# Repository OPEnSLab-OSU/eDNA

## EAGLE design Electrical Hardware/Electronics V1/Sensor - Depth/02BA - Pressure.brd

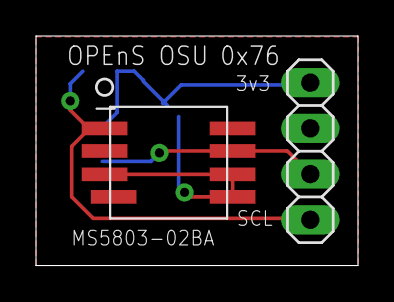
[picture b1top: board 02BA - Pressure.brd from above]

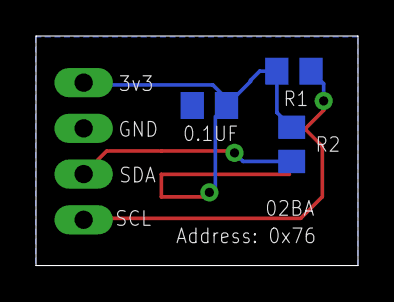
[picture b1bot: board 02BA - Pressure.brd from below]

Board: 2 copper layers, 17.9 x 12.8 mm, 5 parts (3 on the bottom side), 4 nets.

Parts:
0.1UF: 100nF; C0805
JP1: 1X04
PRESSURE: MS5803-01BA; SMD
R1, R2: 7.7k; R0805

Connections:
+3V3: 0.1UF.2, JP1.1, PRESSURE.CSB, PRESSURE.PS, PRESSURE.VDD, R1.2, R2.2
GND: 0.1UF.1, JP1.2
SCL: JP1.4, PRESSURE.SCLK, R1.1
SDA: JP1.3, PRESSURE.SDI/SDA, R2.1

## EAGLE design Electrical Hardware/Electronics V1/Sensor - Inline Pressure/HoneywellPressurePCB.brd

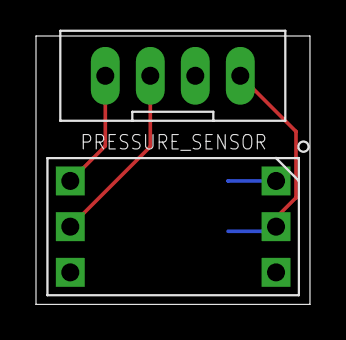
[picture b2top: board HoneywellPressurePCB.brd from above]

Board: 2 copper layers, 15.2 x 14.9 mm, 3 parts (1 on the bottom side), 4 nets.

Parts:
0.1UF: C1206
JST: JST_4POS_2.5MM_UP
PRESSURE_SENSOR: HONEYWELL_PRESSURE_SENSOR; DIP6

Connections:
3V3: 0.1UF.2, JST.4, PRESSURE_SENSOR.2
GND: 0.1UF.1, JST.3, PRESSURE_SENSOR.1
SCL: JST.1, PRESSURE_SENSOR.6
SDA: JST.2, PRESSURE_SENSOR.5

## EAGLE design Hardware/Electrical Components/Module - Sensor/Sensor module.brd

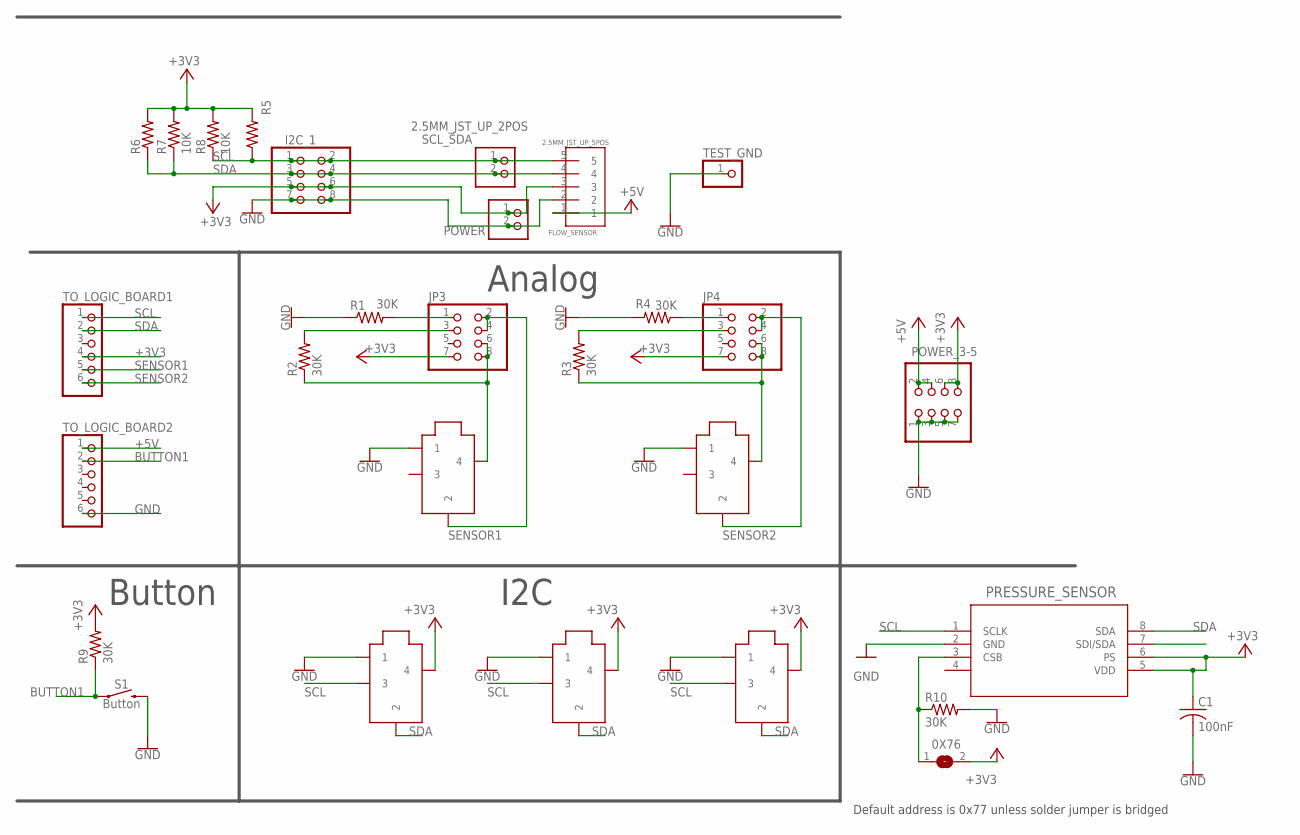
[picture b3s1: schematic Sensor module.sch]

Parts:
0X76: SJ
ANALOG1, ANALOG2: AUDIOJACK_2.5MM_SMD; AJ_2.5_SMD
C1: 100nF; C1206
FLOW_SENSOR: 2.5MM_JST_UP_5POS; JST_5POS_2.5MM_UP
I2C_1: PINHD-2X4; 2X04
JP3, JP4: PINHD-2X4; 2X04
POWER: 2.5MM_JST_UP_2POS; JST_2POS_2.5MM_UP
POWER_3-5: PINHD-2X4; 2X04
PRESSURE_SENSOR: MS580302BA01-00; MS5803-02BA01
R1, R2, R3, R4, R9, R10: 30K; R1206
R5, R6: R-US_R1206; R1206
R7, R8: 10K; 0204/7
S1: Button; TACTILE_SWITCH_PTH_6.0MM
SCL_SDA: 2.5MM_JST_UP_2POS; JST_2POS_2.5MM_UP
TEST_GND: PINHD-1X1; 1X01
TO_LOGIC_BOARD1, TO_LOGIC_BOARD2: PINHD-1X6CB; 1X06-CLEANBIG
U$1, U$2, U$5: I2C; AJ_2.5_SMD

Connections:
+3V3: 0X76.2, C1.1, FLOW_SENSOR.3, I2C_1.5, I2C_1.6, JP3.7, JP4.7, POWER.1, POWER_3-5.6, POWER_3-5.8, PRESSURE_SENSOR.5 (VDD), PRESSURE_SENSOR.6 (PS), R5.2, R6.2, R7.2, R8.2, R9.2, TO_LOGIC_BOARD1.4, U$1.4, U$2.4, U$5.4
+5V: FLOW_SENSOR.1, POWER_3-5.2, POWER_3-5.4, TO_LOGIC_BOARD2.1
BUTTON1: R9.1, S1.1, TO_LOGIC_BOARD2.2
GND: ANALOG1.1, ANALOG2.1, C1.2, FLOW_SENSOR.2, I2C_1.7, I2C_1.8, POWER.2, POWER_3-5.1, POWER_3-5.3, POWER_3-5.5, POWER_3-5.7, PRESSURE_SENSOR.2 (GND), R1.1, R4.2, R10.2, S1.3 (2), TEST_GND.1, TO_LOGIC_BOARD2.6, U$1.1, U$2.1, U$5.1
unnamed: 0X76.1, PRESSURE_SENSOR.3 (CSB), R10.1
unnamed: ANALOG1.4, JP3.6, JP3.8, R2.1
unnamed: JP3.3, R2.2
unnamed: JP3.1, R1.2
unnamed: JP4.3, R3.2
unnamed: ANALOG2.4, JP4.6, JP4.8, R3.1
unnamed: JP4.1, R4.1
SCL: FLOW_SENSOR.5, I2C_1.1, I2C_1.2, PRESSURE_SENSOR.1 (SCLK), R5.1, R8.1, SCL_SDA.1, TO_LOGIC_BOARD1.1, U$1.3, U$2.3, U$5.3
SDA: FLOW_SENSOR.4, I2C_1.3, I2C_1.4, PRESSURE_SENSOR.8 (SDA), R6.1, R7.1, SCL_SDA.2, TO_LOGIC_BOARD1.2, U$1.2, U$2.2, U$5.2
SENSOR1: ANALOG1.2, JP3.2, JP3.4, TO_LOGIC_BOARD1.5
SENSOR2: ANALOG2.2, JP4.2, JP4.4, TO_LOGIC_BOARD1.6

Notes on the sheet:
I2C
Analog
Button
Default address is 0x77 unless solder jumper is bridged

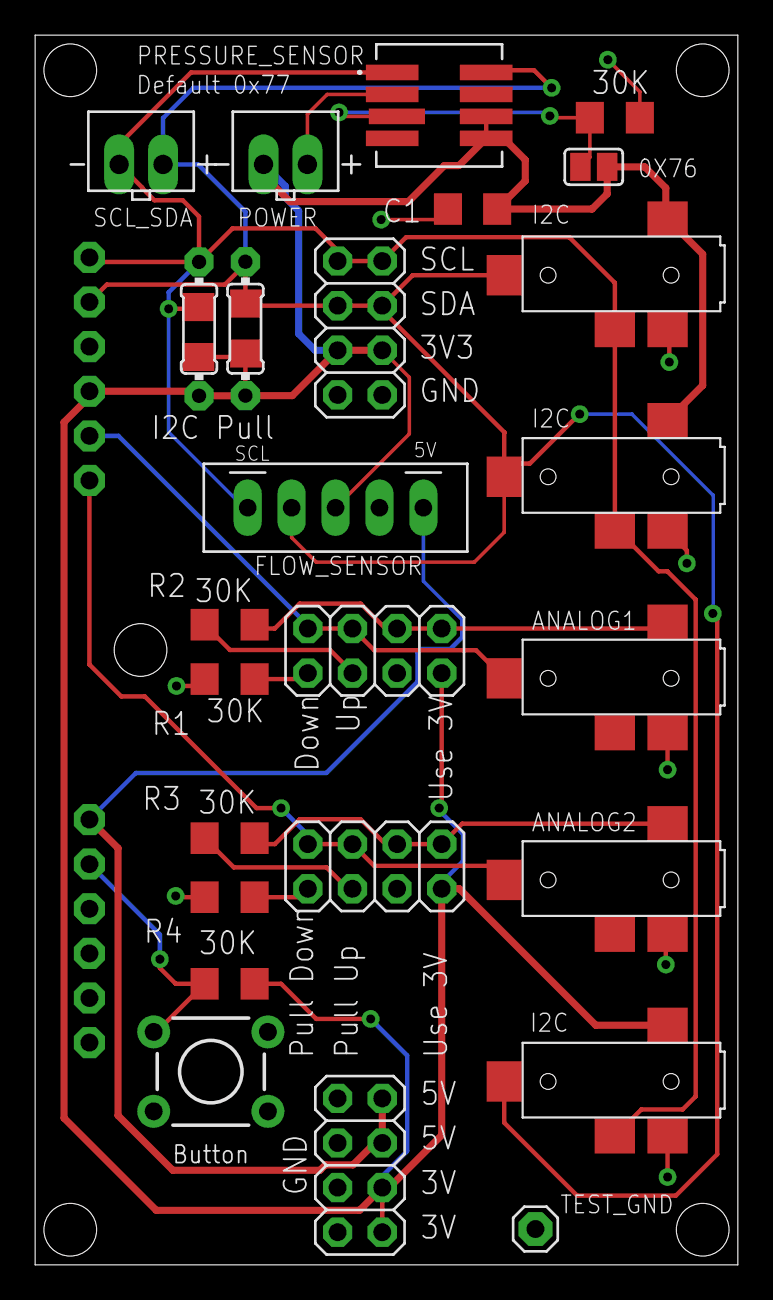
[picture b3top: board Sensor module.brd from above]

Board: 2 copper layers, 40.0 x 70.0 mm, 29 parts (0 on the bottom side), 15 nets.

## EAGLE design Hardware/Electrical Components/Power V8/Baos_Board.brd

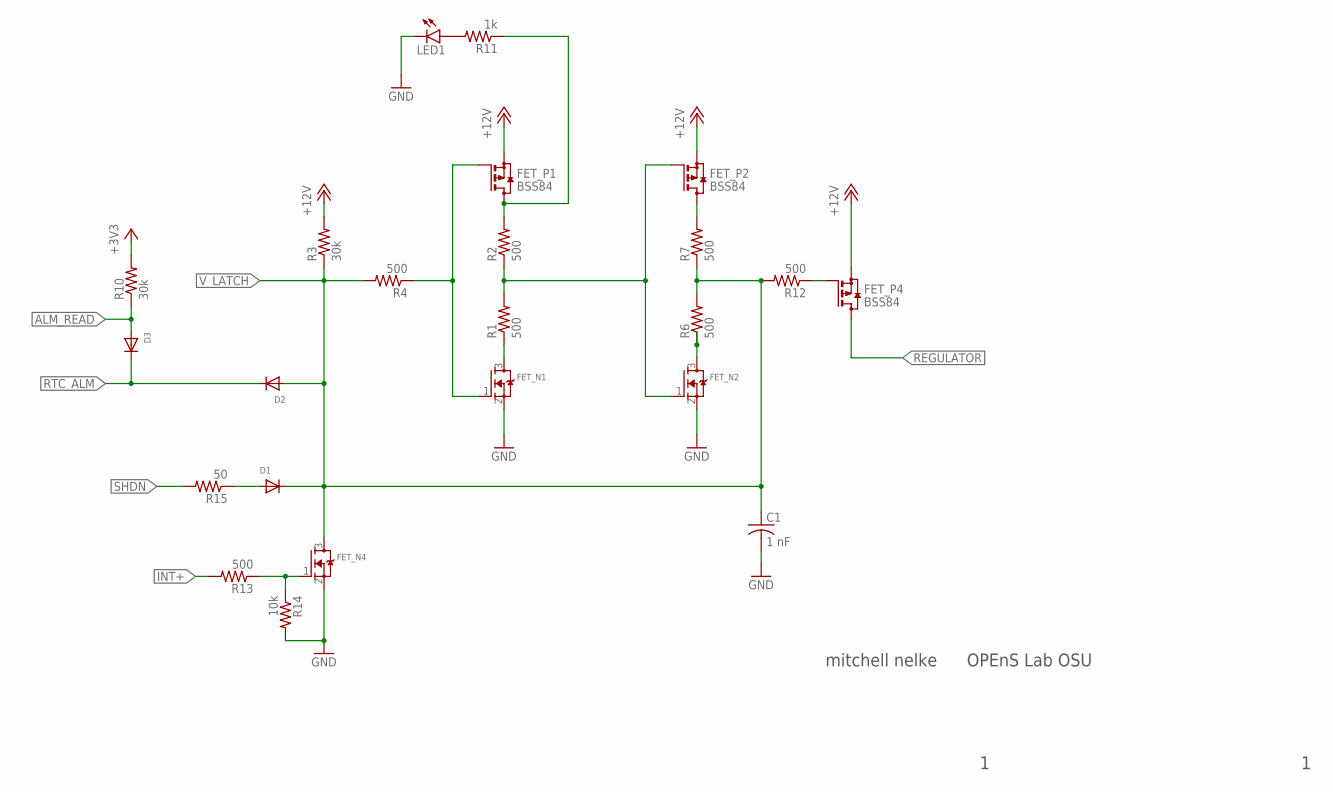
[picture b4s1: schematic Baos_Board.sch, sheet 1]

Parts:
C1: 1 nF; C0805
D1, D2, D3: DIODESOD-123; SOD-123
FET_N1, FET_N2, FET_N4: MOSFET-NREFLOW; SOT23
FET_P1, FET_P2, FET_P4: BSS84; SOT23
LED1: LEDSMT1206; 1206
R1, R2, R4, R6, R7, R12, R13: 500; R0805
R3, R10: 30k; R0805
R11: 1k; R0805
R14: 10k; R0805
R15: 50; R0805

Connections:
+3V3: R10.2; also elsewhere on the board
+12V: FET_P1.2 (S), FET_P2.2 (S), FET_P4.2 (S), R3.2; also elsewhere on the board
ALM_READ: D3.A, R10.1; also elsewhere on the board
GND: C1.2, FET_N1.2 (S), FET_N2.2 (S), FET_N4.2 (S), LED1.C, R14.2; also elsewhere on the board
INT+: R13.2
unnamed: FET_P1.3 (D), R2.2, R11.1
unnamed: FET_N1.3 (D), R1.1
unnamed: FET_N1.1 (G), FET_P1.1 (G), R4.1
unnamed: FET_N2.1 (G), FET_P2.1 (G), R1.2, R2.1
unnamed: FET_P2.3 (D), R7.2
unnamed: FET_N2.3 (D), R6.1
unnamed: LED1.A, R11.2
unnamed: FET_P4.1 (G), R12.1
unnamed: D1.A, R15.1
unnamed: FET_N4.1 (G), R13.1, R14.1
REGULATOR: FET_P4.3 (D); also elsewhere on the board
RTC_ALM: D2.C, D3.C; also elsewhere on the board
SHDN: R15.2; also elsewhere on the board
V_LATCH: C1.1, D1.C, D2.A, FET_N4.3 (D), R3.1, R4.2, R6.2, R7.1, R12.2; also elsewhere on the board

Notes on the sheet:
mitchell nelke
OPEnS Lab OSU

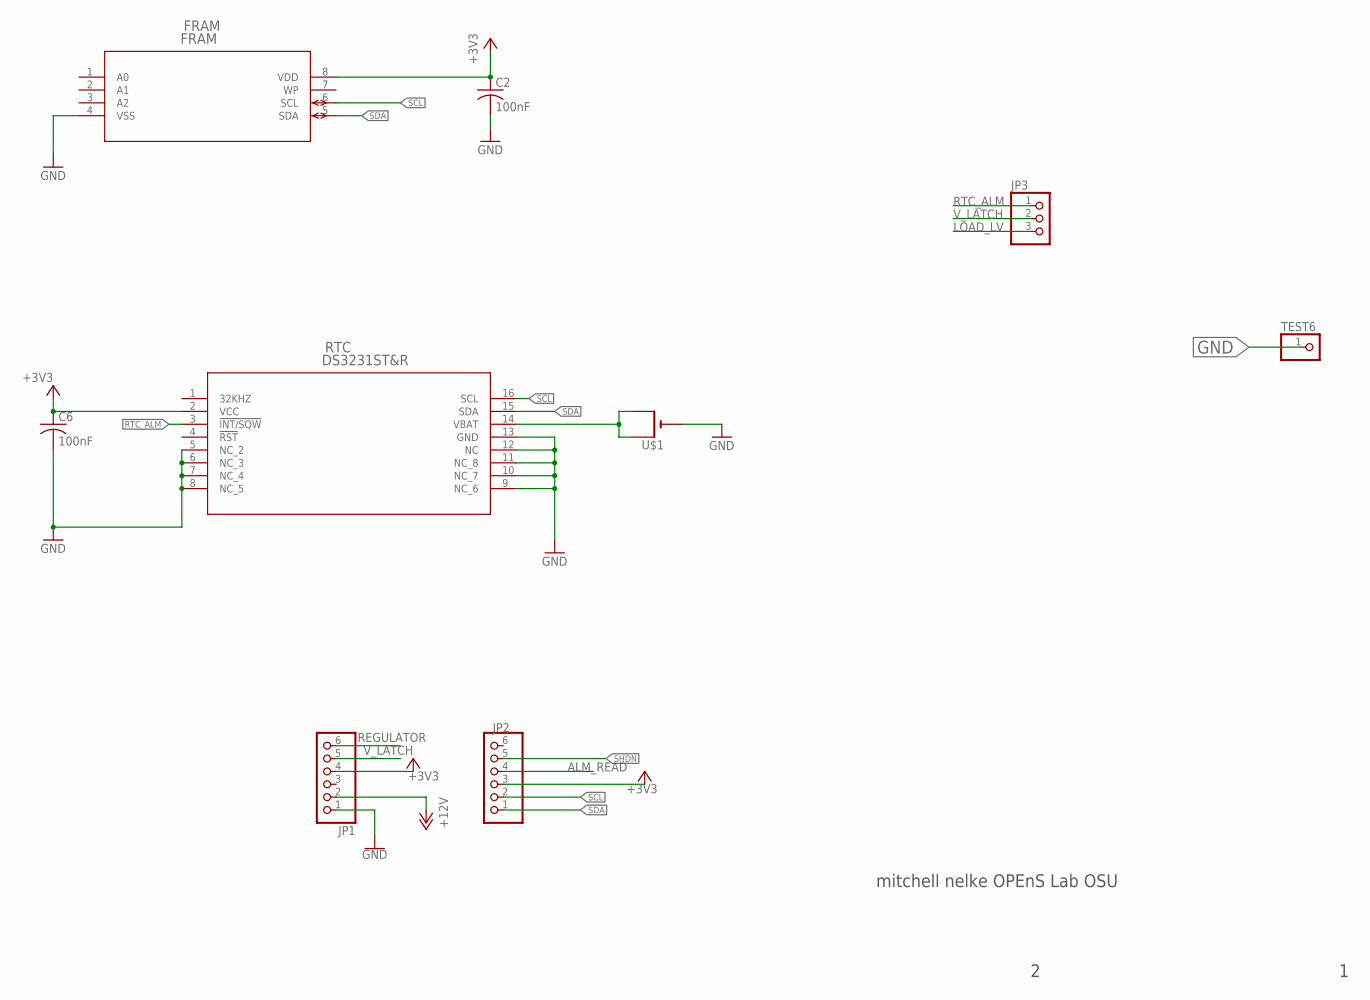
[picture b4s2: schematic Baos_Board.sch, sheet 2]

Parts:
C2, C6: 100nF; C0805
FRAM: FRAM; FPT-8P-M02
JP1, JP2: PINHD-1X6; 1X06
JP3: PINHD-1X3; 1X03
RTC: DS3231ST&R; 21-0042B_16
TEST6: PINHD-1X1; 1X01
U$1: CR1220SMT; CR1220-SMD

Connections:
+3V3: C2.1, C6.1, FRAM.8 (VDD), JP1.4, JP2.3, RTC.2 (VCC); also elsewhere on the board
+12V: JP1.2; also elsewhere on the board
ALM_READ: JP2.4; also elsewhere on the board
GND: C2.2, C6.2, FRAM.4 (VSS), JP1.1, RTC.5 (NC_2), RTC.6 (NC_3), RTC.7 (NC_4), RTC.8 (NC_5), RTC.9 (NC_6), RTC.10 (NC_7), RTC.11 (NC_8), RTC.12 (NC), RTC.13 (GND), TEST6.1, U$1.-; also elsewhere on the board
LOAD_LV: JP3.3
unnamed: RTC.14 (VBAT), U$1.+$1 (+), U$1.+$2 (+1)
REGULATOR: JP1.6; also elsewhere on the board
RTC_ALM: JP3.1, RTC.3 (!INT/SQW); also elsewhere on the board
SCL: FRAM.6 (SCL), JP2.2, RTC.16 (SCL)
SDA: FRAM.5 (SDA), JP2.1, RTC.15 (SDA)
SHDN: JP2.5; also elsewhere on the board
V_LATCH: JP1.5, JP3.2; also elsewhere on the board

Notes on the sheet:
mitchell nelke OPEnS Lab OSU

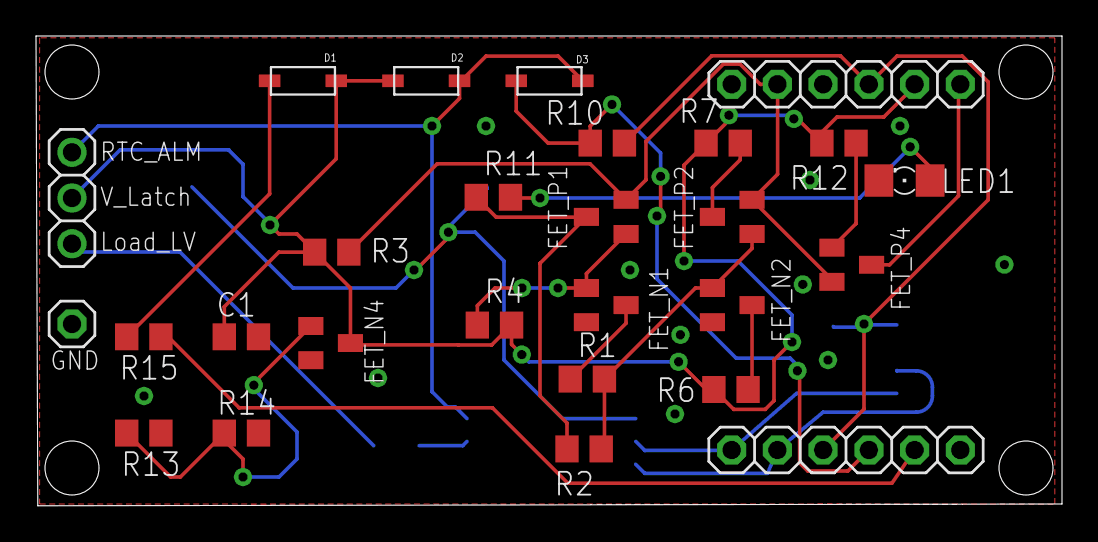
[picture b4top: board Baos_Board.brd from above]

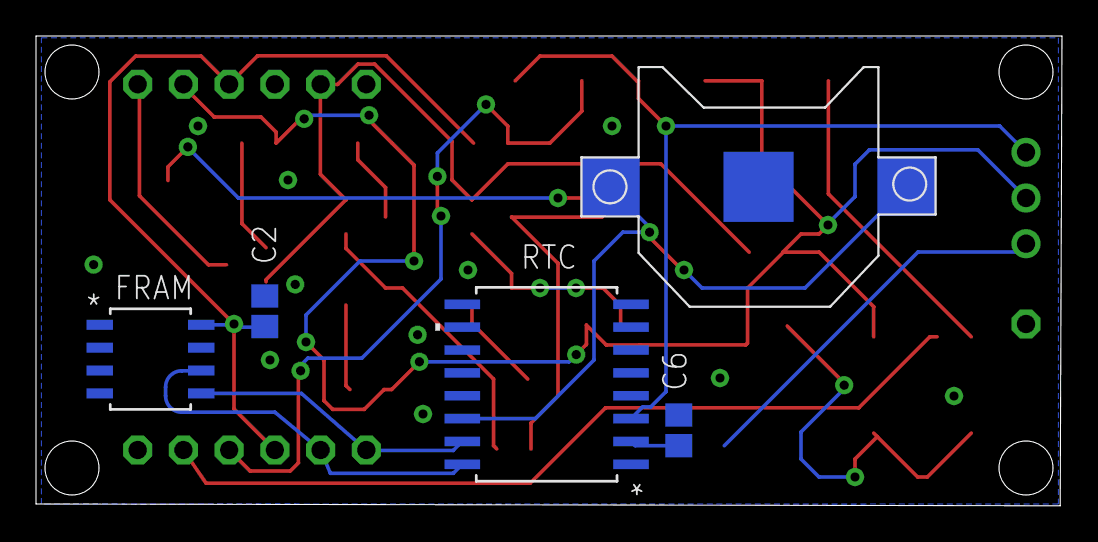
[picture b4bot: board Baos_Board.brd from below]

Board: 2 copper layers, 57.0 x 26.1 mm, 32 parts (5 on the bottom side), 21 nets.

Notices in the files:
parts and their libraries:
SparkFun-PowerSymbols: Licensing: Creative Commons ShareAlike 4.0 International - https://creativecommons.org/licenses/by-sa/4.0
